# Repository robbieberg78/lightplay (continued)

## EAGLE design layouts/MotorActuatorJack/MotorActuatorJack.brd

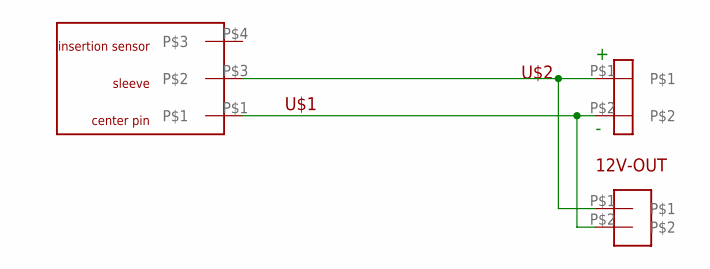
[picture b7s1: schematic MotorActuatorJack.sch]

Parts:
12V-OUT: 1X2HEADER_ROBBIE
U$1: PJ-014CH-SMT
U$2: 3.5MM_2PIN_SCREWTERMINAL_SPARKFUN; 1X02_3.5_SCREWTERM

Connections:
unnamed: 12V-OUT.P$1, U$1.P$3, U$2.P$1
unnamed: 12V-OUT.P$2, U$1.P$1, U$2.P$2

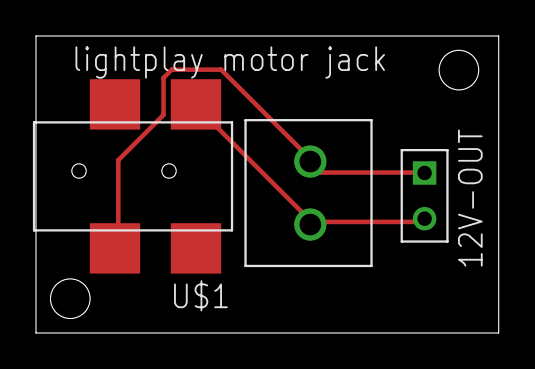
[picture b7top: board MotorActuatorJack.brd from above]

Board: 2 copper layers, 25.7 x 16.5 mm, 3 parts (0 on the bottom side), 2 nets.

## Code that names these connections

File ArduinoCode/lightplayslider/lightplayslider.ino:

int led1 = 3;
 int led2 = 5;
 int led3 = 6;
 int led4 = 9;

int red = led1;
int green = led2;
int blue = led3;
int white = led4;

 
 int analogPin = 0;
 int octant = 0;
 int val = 0;
 int rem = 0;
 int firstpin = 0;
 int secondpin = 0;
 
void setup() {
//Serial.begin(9600);
pinMode(13, OUTPUT);
pinMode(led1, OUTPUT);
pinMode(led2, OUTPUT);
pinMode(led3, OUTPUT);
pinMode(led4, OUTPUT);

digitalWrite(red, HIGH);
digitalWrite(green, LOW);
digitalWrite(blue, LOW);
digitalWrite(white, LOW);
delay(20);

digitalWrite(red, LOW);
digitalWrite(green, HIGH);
digitalWrite(blue, LOW);
digitalWrite(white, LOW);
delay(20);

digitalWrite(red, LOW);
digitalWrite(green, LOW);
digitalWrite(blue, HIGH);
digitalWrite(white, LOW);
delay(20);

digitalWrite(red, LOW);
digitalWrite(green, LOW);
digitalWrite(blue, LOW);
digitalWrite(white, HIGH);
delay(20);

digitalWrite(white, LOW);


}

void loop() {
 


  val = 1023 - analogRead(analogPin);
  octant = (val /128) + 1;
  //rem = val % 256;
 // Serial.println(rem);

  
  switch (octant) {
    case 1:
      digitalWrite(red, HIGH);
      digitalWrite(green, LOW);
      digitalWrite(blue, LOW);
      digitalWrite(white, LOW);
    break;

    case 2:
    digitalWrite(blue, LOW);
    digitalWrite(white, LOW);
    for (int i = 0; i <= 10; i++){
      digitalWrite(red, LOW);
      digitalWrite(green, HIGH);
      delay(2);
      digitalWrite(green, LOW);
      digitalWrite(red, HIGH);
      delay(2);
    }
    

    break;
    
    case 3:
      digitalWrite(red, LOW);
      digitalWrite(green, HIGH);
      digitalWrite(blue, LOW);
      digitalWrite(white, LOW);
      break;

    case 4:
    digitalWrite(red, LOW);
    digitalWrite(white, LOW);
    for (int i = 0; i <= 10; i++){
      digitalWrite(green, LOW);
      digitalWrite(blue, HIGH);
      delay(2);
      digitalWrite(blue, LOW);
      digitalWrite(green, HIGH);
      delay(2);
    }
          
    
    case 5:
      digitalWrite(red, LOW);
      digitalWrite(green, LOW);
      digitalWrite(blue, HIGH);
      digitalWrite(white, LOW);
    break;

    case 6:
    digitalWrite(green, LOW);
    digitalWrite(white, LOW);
    for (int i = 0; i <= 10; i++){
      digitalWrite(red, LOW);
      digitalWrite(blue, HIGH);
      delay(2);
      digitalWrite(blue, LOW);
      digitalWrite(red, HIGH);
      delay(2);
    }
    break;
 
    case 7:
    digitalWrite(green, LOW);
    digitalWrite(blue, LOW);
    for (int i = 0; i <= 10; i++){
      digitalWrite(red, LOW);
      digitalWrite(white, HIGH);
      delay(2);
      digitalWrite(white, LOW);
      digitalWrite(red, HIGH);
      delay(2);
    }
                
    case 8:
      digitalWrite(red, LOW);
      digitalWrite(green, LOW);
      digitalWrite(blue, LOW);
      digitalWrite(white, HIGH);
    break;
  }

//  digitalWrite(firstpin, HIGH);
//  digitalWrite(secondpin, LOW);
//  for (int i = 0; i <= rem; i++){
//    delayMicroseconds(100);
//  }
//
//   digitalWrite(firstpin, LOW);
//   digitalWrite(secondpin, HIGH);  
//  for (int i = rem; i <= 255; i++){
//    delayMicroseconds(100);
//    }

  }

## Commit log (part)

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2015-06-16 test added ben's file
    blah
2015-06-16 dummy index
2015-06-16 Cross domain in lieu of index
2015-06-16 from LLK
2015-06-18 moved LightPlay.py to new python_plugin directory
2015-06-19 initial commit ajax based extension for python-to-arduino server
2015-06-19 typo fix
2015-06-19 added debugging
2015-06-19 fixing cross domain error
2015-06-19 added on/off send interface
2015-06-19 added register block
2015-06-19 typo fixes
2015-06-19 daemonized server
2015-06-19 Changed on block from reporter to command
2015-06-19 aded comment
2015-06-19 removed polling to test on off commands
2015-06-19 test command wait block
2015-06-19 changed on block to asynchronous command
2015-06-20 Please, please, please, don't check in .pyc files.
2015-06-20 Improved TestLightPLayer
    - don't prompt on on/off signals
    - more infromative printing to console
2015-06-21 removed print statement
2015-06-22 formatting changes:wq
2015-06-23 First update with hardware to use to debug
    -Test code now uses arduino class
    -Had to sleep btwn polling to avoid overwhelming serial port
    -Tested to work with scratch ajax_extension
    -run plugin.py to start, ctrl-c to exit
2015-06-23 "old" Scratch Browser plugin that works with serial
2015-06-24 PLEASE STOP CHECKING IN PYC FILES.ADD TO GITIGNORE
    -http://git-scm.com/docs/gitignore Go here, follow directions to
    exxlcude .pyc files
    -In other news, exposed more command line options to plugin.py
    -plugin.py will try and find the correct serial port automatically
    now
2015-06-24 Adding examples, __init__'s, and README
2015-06-24 merging ajax_extension.js
2015-06-24 test adding new blocks to scratch
2015-06-24 removed comma from line 30
2015-06-24 switched to multi block example with hat
2015-06-25 Summary of ScratchX Blocks requested for First Demo
2015-06-25 Adding blocks, cleaning up UI
    -packaged on/off/reverse actions separately
    -refactored js to use common ajax method
    -added poll block
2015-06-25 ajax update
2015-06-25 trying hat blocks for sensors
2015-06-25 bug fixes
2015-06-25 corrected method name for register hat block
2015-06-25 testing
2015-06-25 fixed polling execution context
2015-06-25 fixed callback execution context
2015-06-25 passing polling return value back to extension
2015-06-25 complete ajax call was over-calling my callback
2015-06-25 testing simplified sensor block
2015-06-25 changes to specs for fades and setpower
2015-06-25 created gitignore file for Python complied field etc.
2015-06-26 bug fix
2015-06-26 adding logging to ajax callbacks
2015-06-26 bug fixed, testing sensor manager
2015-06-26 using sensor manager...
2015-06-26 Fixed bug causing python server to block
    -Server is now properly multithreaded
    -Sensor polling is now a (functioning) hat block
    -Sensor polling blocks have to be unique per sensor
    channel, for now. If we could get a block ID or ask the user to
    assign one, this is fixible, otherwise we're in trouble
2015-06-26 changed name of edge detector from 'Wait until' to 'When" to match Scratch convention
2015-06-26 changed default sensor back to 8
2015-06-26 changed default when sensor back to 1
2015-06-28 Eagle files for Light Play v. 1.0
2015-06-28 Data sheets etc for parts used in hardware
2015-06-28 Invoices for Light Play orders
2015-06-28 Bill of Materials for Light Play 1.0 board plus labelling changes to schematic and board
2015-06-29 updated BOM for lightplay hardware
2015-06-30 code cleanup
2015-06-30 added fade in, fade out, setpower and switched sensor reads from digital to analog (mapped to 0 to 100) sensor 1 is read using command = 8, channel =1; sensor 2 is read using command =8, channel =2
2015-06-30 fixed a couple of typos; mainly missing semicolons
2015-06-30 adding new falling/rising sensor behavior
2015-06-30 debug message
2015-06-30 polling bug fix
2015-06-30 analog read, rising and falling edge sensing
2015-06-30 mapped sensor value to 0 to 100
2015-06-30 lowered polling rate to 10 Hz
2015-07-01 added fade blocks
2015-07-01 things are working relatively well...
    -synchronized write access to serial port
    -caught exceptions if device was not ready for reading
    -re-read in instances where device returned None (blocking, probably)
    -may still be some kinks but behaviour seems fairly robust
2015-07-01 Changed initial direction state in arduino.py so that center pin is initially positive
2015-07-01 updated arduino.ino so that turn on resets enable to HIGH 100% of the time
2015-07-06 LightPlay.ino is changed to support non-polling based sensor reads; edge detection done in Arduino.ino and serial writes are done only when an edge is detected. This code also supports request driven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
2015-07-06 Not sure if I saved correctly last time
2015-07-06 update python plugin to be compatible with new.ino
    -moved from polling to async edge updates
    -poll() requests now wait for updates on sensors of interest
2015-07-07 removed "When disconnected" block
2015-07-08 Layout for Tricolor shield added
2015-07-10 update testblue.py to describe protocol for multicolor lamp
2015-07-11 added additional blocks to test bt
    -off block
    -fade block
2015-07-11 made bluetooth support adjustments
    -added serial bt light device
    -changed plugin to detect and add bt light if connected
2015-07-12 new version of Arduino code (Trocolor2) to support tricolor lamp
2015-07-12 bug fixes in plugin, arduino, extension
2015-07-16 added toggle block, robust connection handling
    -toggle block sends opcode 10 to channels
    -At least one device must be connected
    -Having no bt devices prints a warning
2015-07-16 Updated Tricolor3.ino the version of Arduino code for the multicolor lamp
2015-07-16 Some tweaks to the wording of the blocks
2015-07-16 bug fix in sensor updating logic
    -there was an edge case when sensor value was sensor_max
    -this is not may favorite convention, should be done more similarly
    to light protocol
2015-07-17 modified LightPlay,into to support toggle; modified ajax_extension.js to remove "All" option from menu in cases where it is not yet implemented
2015-07-17 added necessary commaa in ajax
2015-07-17 I clearly don't what I'm doing...undo changes to ajax
2015-07-26 Added some invoices and layout for tricolor mini
2015-08-01 Update tricolor mini and lightly arduino code
2015-08-08 Changed LightPlay.ino to include statements that make all 12 motor driver pins outputs, i 9 of the 12 statements were mysteriously missing
2015-08-20 Fixed yellow bug in tricolor mini code; added invoices
2015-08-20 Updated invoices
2015-09-21 Eagle file and BOM for LightPlay 2 added
2015-10-07 Midi changes
    -added some basic midi support using pygame's midi library
2015-10-11 Sample extension for V2 protocol/hardware
    -untested, buyer beware
    -good for prototyping blocks in scratchx
2015-10-11 Tweaking block wording and order
2015-10-12 removed smart quotes that text edit had added
2015-10-19 initial version of lightplay2 arduino code added
2015-10-23 Changees for V2 protocol
2015-10-26 new versions of lightplay2 arduino code and scratch pluin
2015-10-27 updated layout files
2015-10-27 fixed incorrect power names in js
2015-11-07 version 0.2a of layout eagle files added, not yet final
2015-12-22 working on Arduino code for LightPlay2a
2015-12-23 variable fade times now working....
2015-12-26 fades working
2015-12-31 setbrightness now working
2016-01-02 swapped command numbers for motor and setcolor to avoid sending 0x2b (ascii '+'), which Adafruit BTLE UART treats as special character
2016-01-05 tweaked Blocks info so that it is up to date date with current Arduino firmware
2016-01-07 fixed - but haven't yet tested - bug in Arduino code that was breaking fade to surprise
2016-03-09 fixed bug in line 710 of Arduino code that was preventing light2 from fading to
2016-03-28 changed method of changing motorspee to use 100 Hz manual pwm during delay; also changed surprise to prevent choosing the same color twice in a row
2016-05-06 Adding color setting by RGB value
    -Scaling might be wrong, check this
2016-05-06 Added the modernized scratch extension
    -Ues the new scratch device manager framework
    -Communicates via BLE
2016-05-10 Fixed undefined white value
2016-05-10 Revert " Added the modernized scratch extension"
    This reverts commit 233048220d837c88dd14dab2f908c98167806df0.
2016-05-26 added Scratch Device manager
2016-08-19 lots of little changes
2016-09-22 added lots of local changes
2016-10-08 shortened bootflash in lightplay2a arduino code
2016-11-19 started work on lightplay arduino code v2
2016-11-19 working version of arduino code that (iPad only) that uses struct and fixes fadeout bug
2016-11-19 deleted old version
2016-11-20 packets version making progress, non-fading light commands working
2016-11-20 added byte code docx to Ardunino packets folder
2016-11-21 added motor commands but haven't tested with hardware yet
2016-11-21 tweaked command documentation
2016-11-21 tweaked arduino packet code; fixed tfade bug
2016-11-21 added list of csample packet codes
2016-11-21 added sensor streaming, stopall, reset state
2016-11-21 tweaked send sensor to run at 10 Hz
2016-11-21 changed stopall to stop fades, can then issue commands to turn off lights and motors
2016-11-21 fixed bug in struct initilalization; lights[3] -> lights[4]
2016-11-22 fixed surprise bug in non-packet version v2 so that it works in current iPad software
2016-11-26 renamed versions to be compatible with postings on lighyplay-LLK repo
2016-11-26 updated readme file
2016-12-10 started playing with branches
2016-12-10 added sensor sends
2017-01-04 sensor streaming
2017-01-05 new reporting protocol implemneted
2017-01-06 added .gitignore
2017-01-06 deleted old blocks doc files
2017-01-10 fixed bug in sendsensor
2017-01-13 modified firmware to improve fading
2017-01-13 Modified byte code documentation to include changes to stopfades#
2017-01-13 modified firmware so that fades in procegress get aborted by subsequent light commands from other threads. So, for example, if thread 1 issues a fadeto blue command and then one second later thread2 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
2017-01-13 no sig changes here...
2017-01-13 added code to report fadedone each time a fade in process is interupted; this may help host software manage flow of control
2017-01-19 added send firmware version number command (version number is X.Y format with X given by high nibble and Y given by low nibble)
2017-01-19 fixed version send so that response doesn't conflict with sensor values
2017-01-24 Fixed a bug in firmware in lightout.
    There's still a bug which I believe is currently believe is firmware relation that is driving me crazy:
    Interrupted fades are buggy. Here's one reproducible symptom that may hold a clue as to the larger problem:
    I set up the following two threads:
    1) on play [fadeallto green] 2) on play [wait 4 fadealltored]
    When I run it from the lightoff state (either on power up or by executing a lightoff after it's run) the
    cross fades are starnge. But if I run it after a fadeout, the cross fades work normally.
2017-01-29 Fixed bug in Arduino code that was cause fade interrupt strangeness. (in this commit the fixed version in in v2mod, will update v2 in next commit) The problem was that, previously, during a fade upda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
    on play [fadeto green]
    on play [wait 3 fadeto red]
    This executes properly the first time. So the red channel value will be at
